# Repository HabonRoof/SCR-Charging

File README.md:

# Sinusoidal Charger with Optimized Frequency Tracking for Li-ion Batteries

The purpose of this thesis is to develop a sinusoidal charger that can track the optimized frequency of Li-ion batteries.
In this study, the optimized AC impedance frequency tracking is firstly carried out for various types of lithium-ion batteries with different aging degrees to achieve the goal of shortening the charging time and increasing the charging efficiency. 
The digital control core of the charger developed in this thesis uses the F280049C digital signal controller (DSC) produced by Texas Instruments and adopts the Powell algorithm to quickly search for the best sinusoidal charging current frequency when the battery state-of-charge (SOC) is 0%, 15% and 30%, which ensures the lowest impedance during charging.
The proposed prototyping circuit uses field effect transistors as voltage-to-current converters and utilizes digital finite impulse response filters and proportional-integral controllers to stabilize the charging current. 
The charger can provide a maximum charging power of 21W. The experimental results show that the proposed sinusoidal charger can shorten the charging time by 3.66%, reduce the charging loss by 1.08% and reduce the temperature rise by 27.16% compared with the traditional constant current and constant voltage charging method.
Keyword: Sinusoidal Charging, Li-ion Batteries, Fast Charging technique, On-line Optimized Impedance Tracking

[Thesis link](https://ndltd.ncl.edu.tw/cgi-bin/gs32/gsweb.cgi/login?o=dwebmge)

# Outlook

# File disceiption
#### AD5940_BATImpedance
- ADICuP3029 project, to control and calculate real/imaginary part of impedance. Include FFT calculation.
- Source code for AD5940 battery EIS measurment module (CN0510), modified and origin by Analog Device .Inc.
#### KiCad
- Schematic file and PCB file for main board, which offer CN0510, F280049C Launch Pad and AD9833 waveform generator module a base.
#### RippleCharging
- The main CCS project folder, control the behavior of sinusoidal charger, waveform generator, MOSFET relay, EIS measurement module.
#### ad5940lib
- Companion library of AD5940_BATImpedance folder

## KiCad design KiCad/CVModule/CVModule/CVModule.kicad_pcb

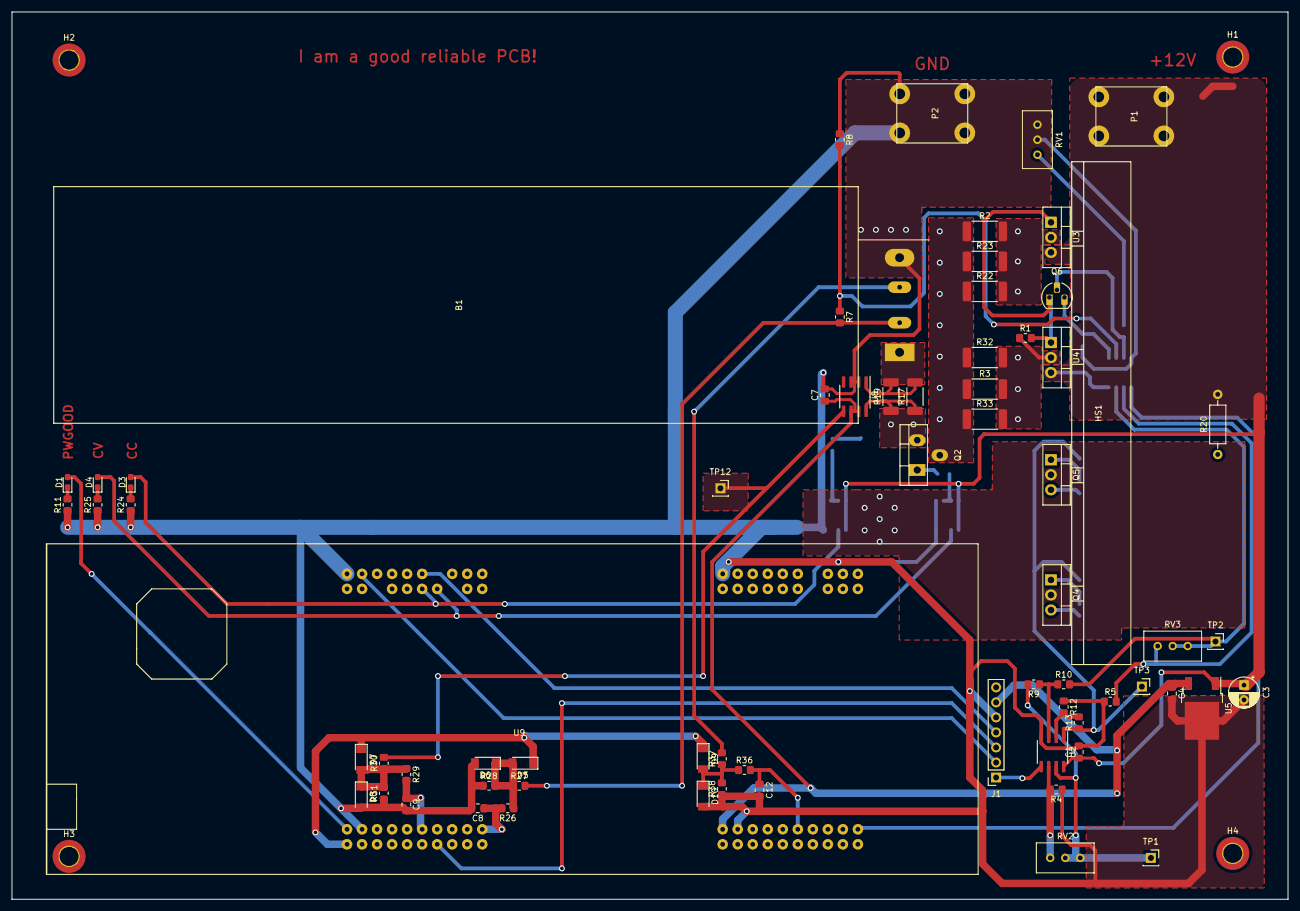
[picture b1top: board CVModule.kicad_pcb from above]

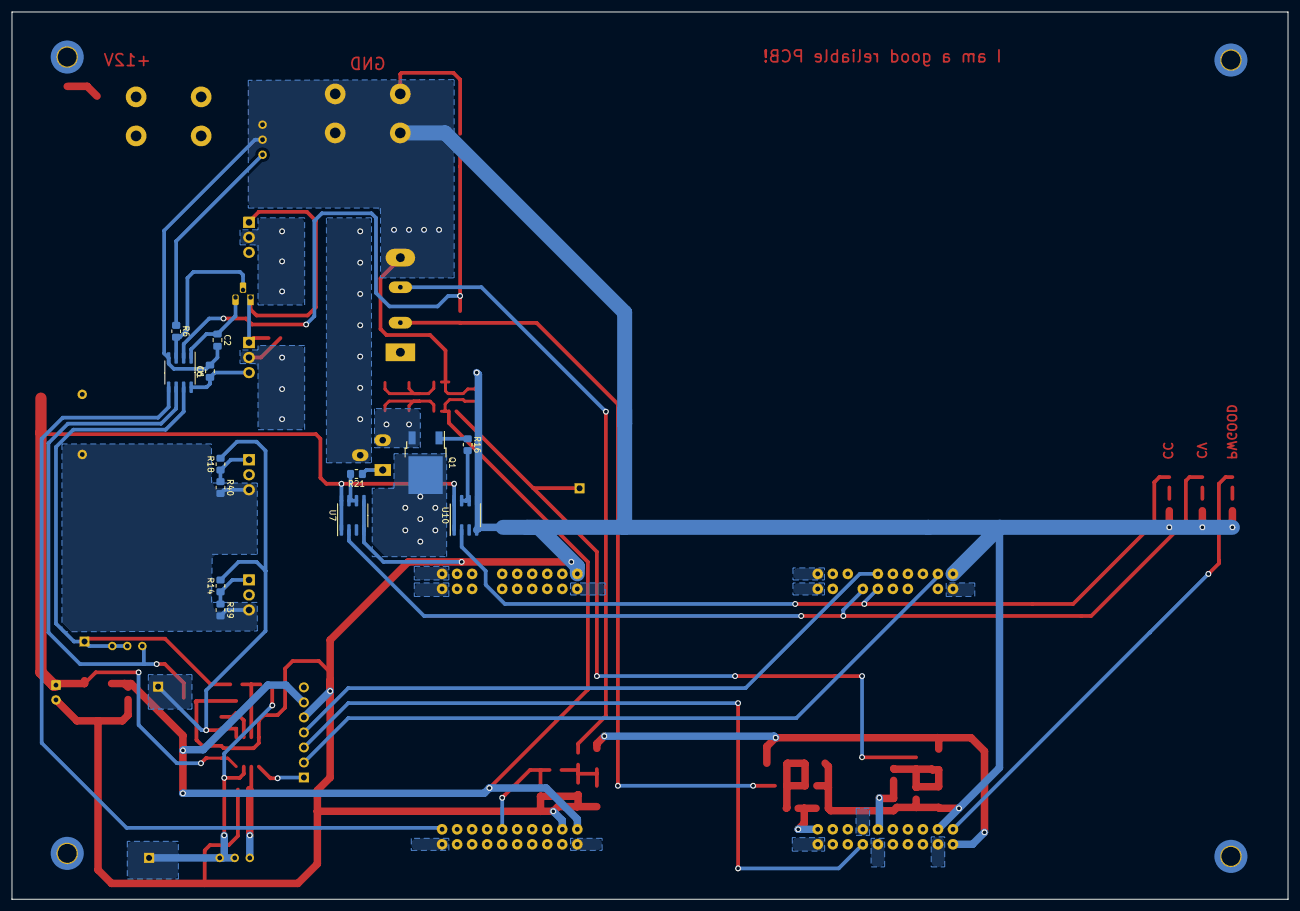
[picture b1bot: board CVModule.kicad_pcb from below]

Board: 2 copper layers, 215.7 x 150.0 mm, 85 parts (13 on the bottom side), 48 nets.

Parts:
B1: BatteryHolder; BatteryHolder-Single
C1, C4, C6, C7, C8, C9, C12: 100n; C_0805_2012Metric_Pad1.18x1.45mm_HandSolder
C2: 180p; C_0805_2012Metric_Pad1.18x1.45mm_HandSolder
C3: 0.33u; CP_Radial_D5.0mm_P2.50mm
D1: GREEN; LED_0603_1608Metric_Pad1.05x0.95mm_HandSolder
D3, D4: RED; LED_0603_1608Metric_Pad1.05x0.95mm_HandSolder
D5, D6, D7, D8, D9, D10: 1N4148; D_MiniMELF
H1, H2, H3, H4: MountingHole; MountingHole_3.2mm_M3_DIN965_Pad_TopBottom
HS1: Heatsink; Heatsink_80mmx3mm_4hole_black
J1: AD9833; PinSocket_1x07_P2.54mm_Vertical
P1: +12Vin; IOPad
P2: GND; IOPad
Q1: 600N25NG; TO-252-2
Q2: IPP030N10N3; TO220-3_Vertical_T
Q4, Q5: IRFR9024; TO-220-3_Vertical
Q6: A733; TO-92_HandSolder
R1, R6: 100; R_0805_2012Metric_Pad1.20x1.40mm_HandSolder
R2, R3, R22, R23, R32, R33: 510m; R_2512_6332Metric_Pad1.40x3.35mm_HandSolder
R4, R11, R12, R24, R25, R26, R29, R36: 1k; R_0805_2012Metric_Pad1.20x1.40mm_HandSolder
R5: 50k; R_0805_2012Metric_Pad1.20x1.40mm_HandSolder
R7, R8: 2M; R_0805_2012Metric_Pad1.20x1.40mm_HandSolder
R9, R10: 100k; R_0805_2012Metric_Pad1.20x1.40mm_HandSolder
R13: 2k; R_0805_2012Metric_Pad1.20x1.40mm_HandSolder
R14, R16, R18, R21: 10; R_0805_2012Metric_Pad1.20x1.40mm_HandSolder
R17, R19: 13m; R_2010_5025Metric_Pad1.40x2.65mm_HandSolder
R20: 0.1/2W; R_Axial_DIN0207_L6.3mm_D2.5mm_P10.16mm_Horizontal
R27, R30, R37: 4.7k; R_0805_2012Metric_Pad1.20x1.40mm_HandSolder
R28, R31, R38, R39, R40: 10k; R_0805_2012Metric_Pad1.20x1.40mm_HandSolder
RV1: 1k; Potentiometer_Bourns_3296W_Vertical
RV2: 2k; Potentiometer_Bourns_3296W_Vertical
RV3: 100k; Potentiometer_Bourns_3296W_Vertical
TP1: sig_TP; PinSocket_1x01_P2.54mm_Vertical
TP2: bias_TP; PinSocket_1x01_P2.54mm_Vertical
TP3: Vg_TP; PinSocket_1x01_P2.54mm_Vertical
TP12: Iout; PinSocket_1x01_P2.54mm_Vertical
U1, U2: LM358; SOIC-8_3.9x4.9mm_P1.27mm
U3, U4: LM317_TO-220; TO-220-3_Vertical
U5: L7805; TO-252-2
U7, U10: TC4420EOA; SOIC-8_3.9x4.9mm_P1.27mm
U8: INA282; SOIC-8_3.9x4.9mm_P1.27mm
U9: LAUNCHXL-F280049C; LANCHXL-F280049C

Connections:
+3V3: D5.1, D7.1, D9.1, U9.1
+4.2V: Q2.2, R2.1, R3.1, R22.1, R23.1, R32.1, R33.1
+5V: C4.1, C7.1, D1.2, J1.6, U5.3, U8.6, U8.7, U9.21, U9.61
+12V: C1.1, C3.1, C6.1, P1.1, R20.2, U1.8, U2.8, U3.3, U4.3, U5.1, U7.1, U7.8, U10.1, U10.8
-BATT: B1.4, C1.2, C2.2, C3.2, C4.2, C6.2, C7.2, C8.2, C9.2, C12.2, D6.2, D8.2, D10.2, J1.5, P2.1, R4.1, R5.1, R8.1, R11.1, R12.1, R24.1, R25.1, R28.1, R31.1, R38.1, RV1.2, RV1.3, U1.4, U2.4, U5.2, U7.4, U7.5, U8.2, U8.3, U9.20, U9.22, U9.60, U9.62, U10.4, U10.5
CC_g: D3.2, U9.35, U10.2
CS: J1.2, U9.19
CV_g: D4.2, U7.2, U9.34
Iout: R30.2, TP12.1, U8.5
MOSI: J1.4, U9.15
unnamed: C2.1, Q6.3, U1.1
unnamed: D1.1, R11.2
unnamed: D3.1, R24.2
unnamed: D4.1, R25.2
unnamed: D5.2, D6.1, R26.1, R27.1, R28.2
unnamed: D7.2, D8.1, R29.1, R30.1, R31.2
unnamed: D9.2, D10.1, R36.1, R37.1, R38.2
unnamed: Q1.1, R16.1
unnamed: Q1.2, Q4.2, Q5.2
unnamed: Q2.1, R21.1
unnamed: Q4.1, R14.1, R39.1
unnamed: Q4.3, Q5.3, R20.1, R39.2, R40.2
unnamed: Q5.1, R18.1, R40.1
unnamed: Q6.1, R1.2, U3.1, U4.1
unnamed: Q6.2, R6.2, U1.3
unnamed: R1.1, R3.2, R32.2, R33.2, U4.2
unnamed: R2.2, R22.2, R23.2, U3.2
unnamed: R4.2, RV2.3, U2.6
unnamed: R5.2, RV3.3, U1.6
unnamed: R6.1, RV1.1
unnamed: R7.1, R8.2, U1.2
unnamed: R9.2, RV2.1, RV2.2, TP1.1, U2.7
unnamed: R9.1, R10.1, U2.3
unnamed: R10.2, RV3.1, RV3.2, TP2.1, U1.7
unnamed: R12.2, R13.2, U2.2
Q1_g: R16.2, U10.6, U10.7
Q2_g: R21.2, U7.6, U7.7
Rs+: Q1.3, Q2.3, R17.1, R19.1, U8.8
Rs-: B1.1, R17.2, R19.2, U8.1
SCLK: J1.3, U9.7
Vbat+: C8.1, R26.2, U9.30
Vbat-: C12.1, R36.2, U9.66
Viout: C9.1, R29.2, U9.26
bat+: B1.2, R7.2, R27.2
bat-: B1.3, R37.2
bias_ctl: U1.5, U9.70
signal: R13.1, R14.2, R18.2, TP3.1, U2.1
sigout: J1.1, U2.5

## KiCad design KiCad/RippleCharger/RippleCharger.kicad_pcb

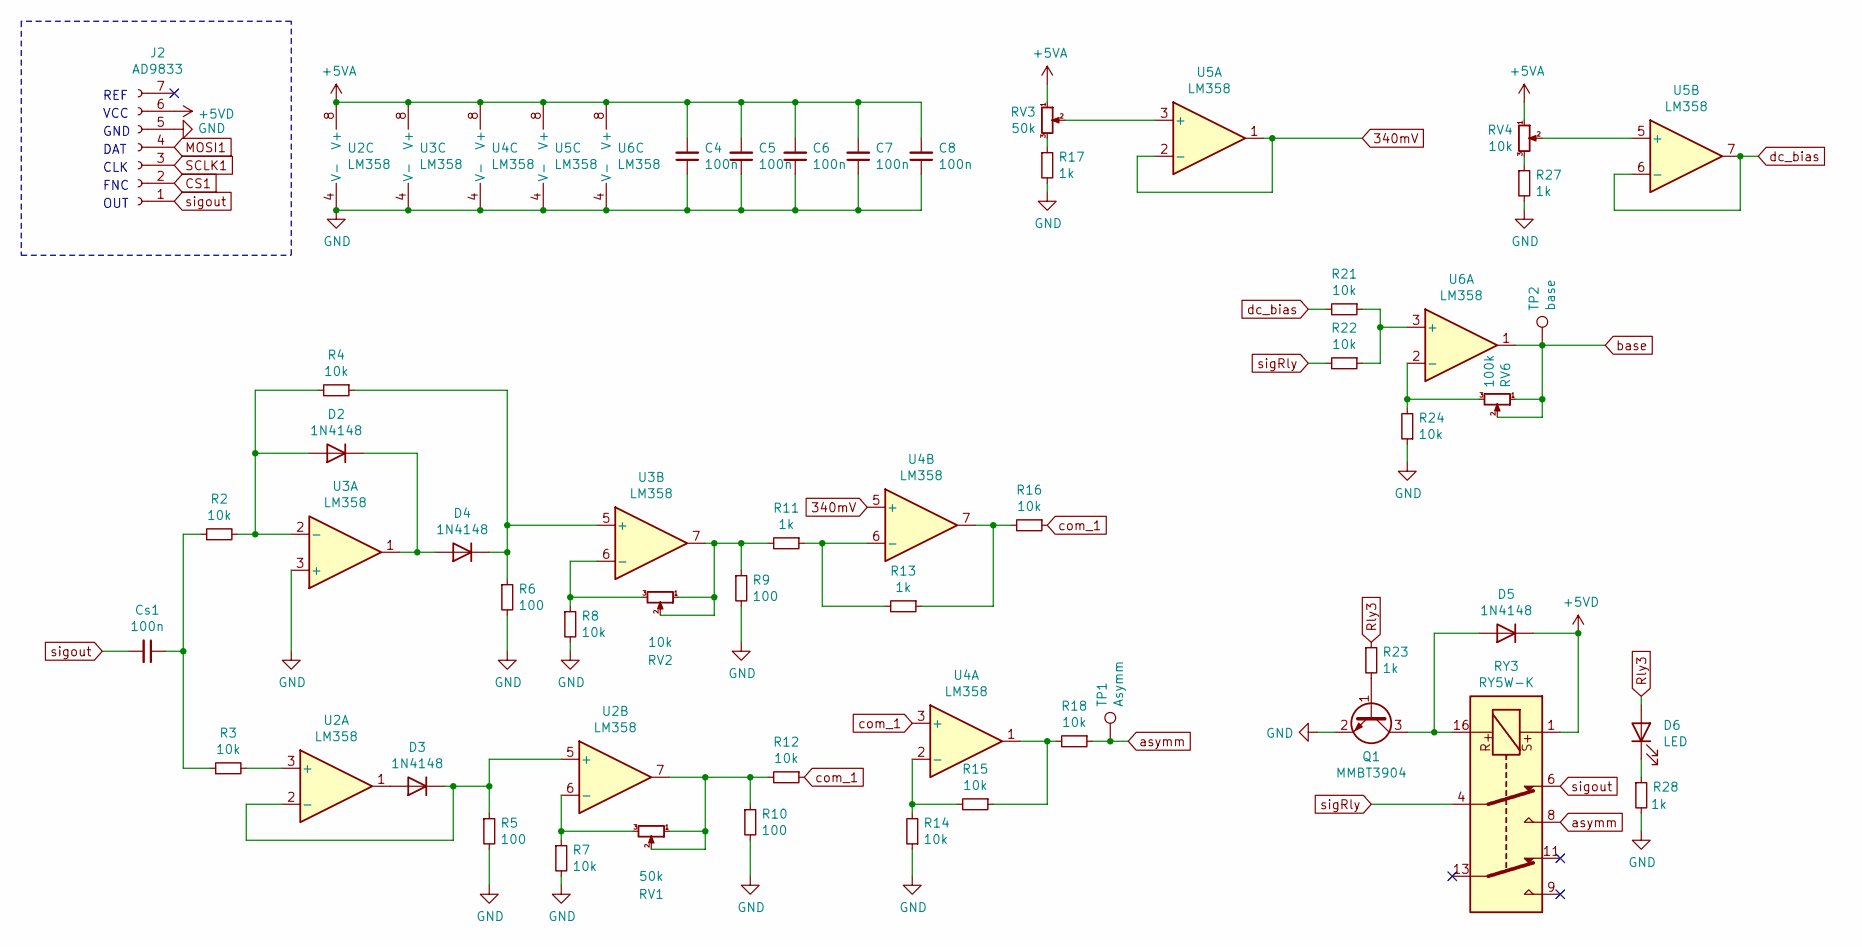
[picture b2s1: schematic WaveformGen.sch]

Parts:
C4, C5, C6, C7, C8: 100n; C_0805_2012Metric_Pad1.18x1.45mm_HandSolder
Cs1: 100n; C_0805_2012Metric_Pad1.18x1.45mm_HandSolder
D2, D3, D4, D5: 1N4148; D_SOD-123
D6: LED; LED_0603_1608Metric_Pad1.05x0.95mm_HandSolder
J2: AD9833; PinHeader_1x07_P2.54mm_Vertical
Q1: MMBT3904; SOT-23
R2, R3, R4, R7, R8, R12, R14, R15, R16, R18, R21, R22, R24: 10k; R_0805_2012Metric_Pad1.20x1.40mm_HandSolder
R5, R6, R9, R10: 100; R_0805_2012Metric_Pad1.20x1.40mm_HandSolder
R11, R13, R17, R23, R27, R28: 1k; R_0805_2012Metric_Pad1.20x1.40mm_HandSolder
RV1, RV3: 50k; Potentiometer_Bourns_3296W_Vertical
RV2, RV4: 10k; Potentiometer_Bourns_3296W_Vertical
RV6: 100k; Potentiometer_Bourns_3296W_Vertical
RY3: RY5W-K
TP1: Asymm; PinHeader_1x01_P2.54mm_Vertical
TP2: base; PinHeader_1x01_P2.54mm_Vertical
U2, U3, U4, U5, U6: LM358; SOIC-8_3.9x4.9mm_P1.27mm

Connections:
340mV: U4.5 (+), U5.1, U5.2 (-)
+5VA: C4.2, C5.2, C6.2, C7.2, C8.2, RV3.1, RV4.1, U2.8 (V+), U3.8 (V+), U4.8 (V+), U5.8 (V+), U6.8 (V+); also elsewhere on the board
+5VD: D5.1 (K), J2.6, RY3.1; also elsewhere on the board
CS1: J2.2; also elsewhere on the board
GND: C4.1, C5.1, C6.1, C7.1, C8.1, J2.5, Q1.2 (E), R5.2, R6.2, R7.2, R8.2, R9.2, R10.2, R14.1, R17.2, R24.1, R27.2, R28.2, U2.4 (V-), U3.3 (+), U3.4 (V-), U4.4 (V-), U5.4 (V-), U6.4 (V-); also elsewhere on the board
MOSI1: J2.4; also elsewhere on the board
unnamed: Cs1.1, R2.1, R3.1
unnamed: D2.1 (K), D4.2 (A), U3.1
unnamed: D2.2 (A), R2.2, R4.2, U3.2 (-)
unnamed: D3.1 (K), R5.1, U2.2 (-), U2.5 (+)
unnamed: D3.2 (A), U2.1
unnamed: D4.1 (K), R4.1, R6.1, U3.5 (+)
unnamed: D5.2 (A), Q1.3 (C), RY3.16
unnamed: D6.1 (K), R28.1
unnamed: Q1.1 (B), R23.2
unnamed: R3.2, U2.3 (+)
unnamed: R7.1, RV1.3, U2.6 (-)
unnamed: R8.1, RV2.3, U3.6 (-)
unnamed: R10.1, R12.2, RV1.1, RV1.2, U2.7
unnamed: R11.1, R13.2, U4.6 (-)
unnamed: R9.1, R11.2, RV2.1, RV2.2, U3.7
unnamed: R13.1, R16.2, U4.7
unnamed: R14.2, R15.2, U4.2 (-)
unnamed: R15.1, R18.2, U4.1
unnamed: R17.1, RV3.3
unnamed: R21.1, R22.1, U6.3 (+)
unnamed: R24.2, RV6.3, U6.2 (-)
unnamed: R27.1, RV4.3
unnamed: RV3.2, U5.3 (+)
unnamed: RV4.2, U5.5 (+)
Rly3: D6.2 (A), R23.1; also elsewhere on the board
SCLK1: J2.3; also elsewhere on the board
asymm: R18.1, RY3.8, TP1.1
base: RV6.1, RV6.2, TP2.1, U6.1; also elsewhere on the board
com_1: R12.1, R16.1, U4.3 (+)
dc_bias: R21.2, U5.6 (-), U5.7
sigRly: R22.2, RY3.4
sigout: Cs1.2, J2.1, RY3.6

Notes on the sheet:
REF
VCC
GND
DAT
CLK
FNC
OUT

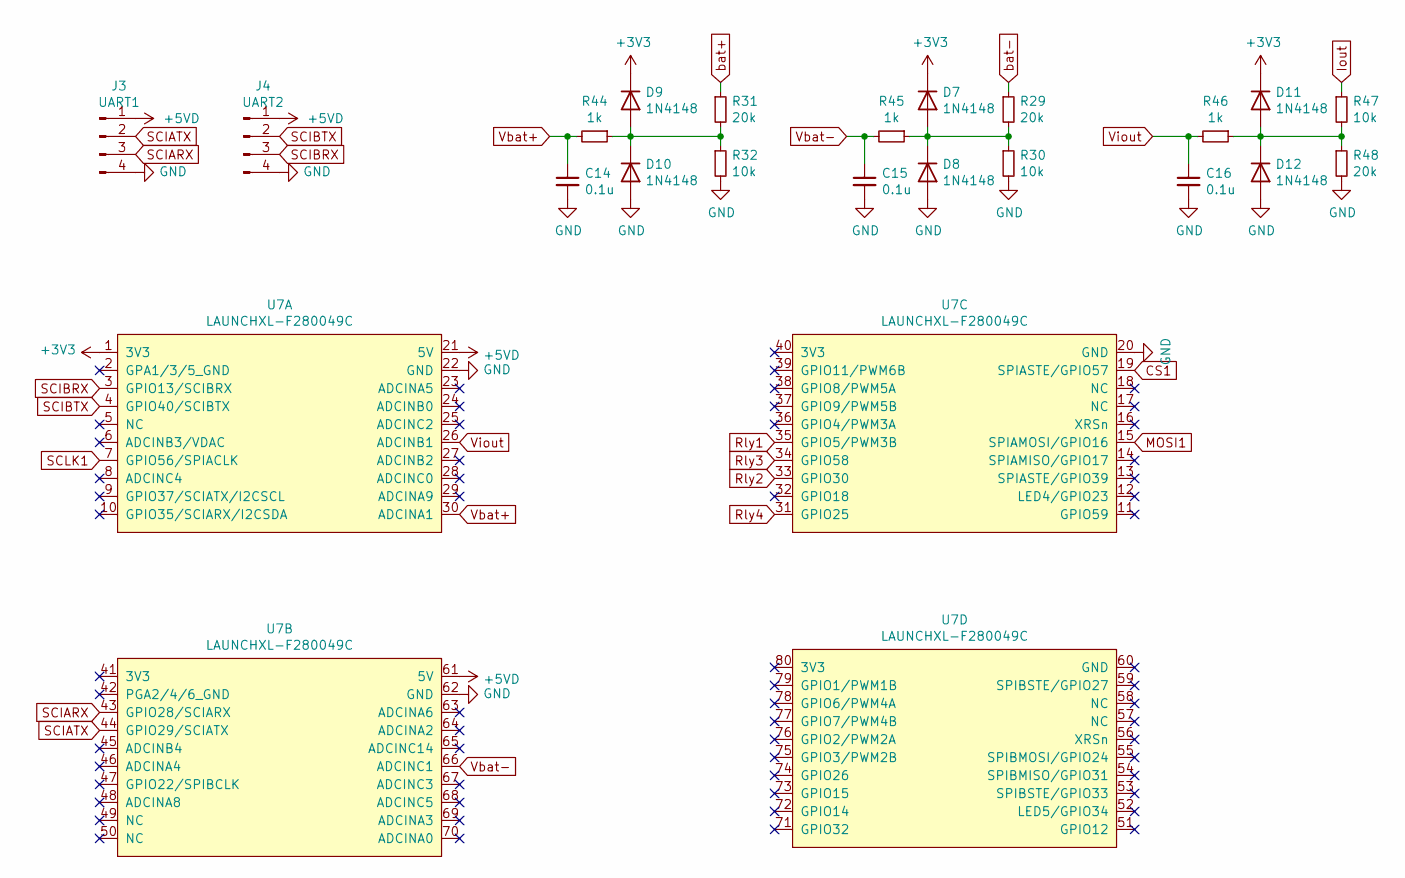
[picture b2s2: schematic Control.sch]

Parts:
C14, C15, C16: 0.1u; C_0805_2012Metric_Pad1.18x1.45mm_HandSolder
D7, D8, D9, D10, D11, D12: 1N4148; D_SOD-123
J3: UART1; PinHeader_1x04_P2.54mm_Vertical
J4: UART2; PinHeader_1x04_P2.54mm_Vertical
R29, R31, R48: 20k; R_0805_2012Metric_Pad1.20x1.40mm_HandSolder
R30, R32, R47: 10k; R_0805_2012Metric_Pad1.20x1.40mm_HandSolder
R44, R45, R46: 1k; R_0805_2012Metric_Pad1.20x1.40mm_HandSolder
U7: LAUNCHXL-F280049C; LANCHXL-F280049C

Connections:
+3V3: D7.1 (K), D9.1 (K), D11.1 (K), U7.1 (3V3)
+5VD: J3.1, J4.1, U7.21 (5V), U7.61 (5V); also elsewhere on the board
CS1: U7.19 (SPIASTE/GPIO57); also elsewhere on the board
GND: C14.2, C15.2, C16.2, D8.2 (A), D10.2 (A), D12.2 (A), J3.4, J4.4, R30.2, R32.2, R48.2, U7.20 (GND), U7.22 (GND), U7.62 (GND); also elsewhere on the board
MOSI1: U7.15 (SPIAMOSI/GPIO16); also elsewhere on the board
unnamed: D7.2 (A), D8.1 (K), R29.2, R30.1, R45.1
unnamed: D9.2 (A), D10.1 (K), R31.2, R32.1, R44.1
unnamed: D11.2 (A), D12.1 (K), R46.1, R47.2, R48.1
Rly1: U7.35 (GPIO5/PWM3B); also elsewhere on the board
Rly2: U7.33 (GPIO30); also elsewhere on the board
Rly3: U7.34 (GPIO58); also elsewhere on the board
Rly4: U7.31 (GPIO25); also elsewhere on the board
SCIARX: J3.3, U7.43 (GPIO28/SCIARX)
SCIATX: J3.2, U7.44 (GPIO29/SCIATX)
SCIBRX: J4.3, U7.3 (GPIO13/SCIBRX)
SCIBTX: J4.2, U7.4 (GPIO40/SCIBTX)
SCLK1: U7.7 (GPIO56/SPIACLK); also elsewhere on the board
Vbat+: C14.1, R44.2, U7.30 (ADCINA1)
Vbat-: C15.1, R45.2, U7.66 (ADCINC1)
Viout: C16.1, R46.2, U7.26 (ADCINB1)
bat+: R31.1; also elsewhere on the board
bat-: R29.1; also elsewhere on the board

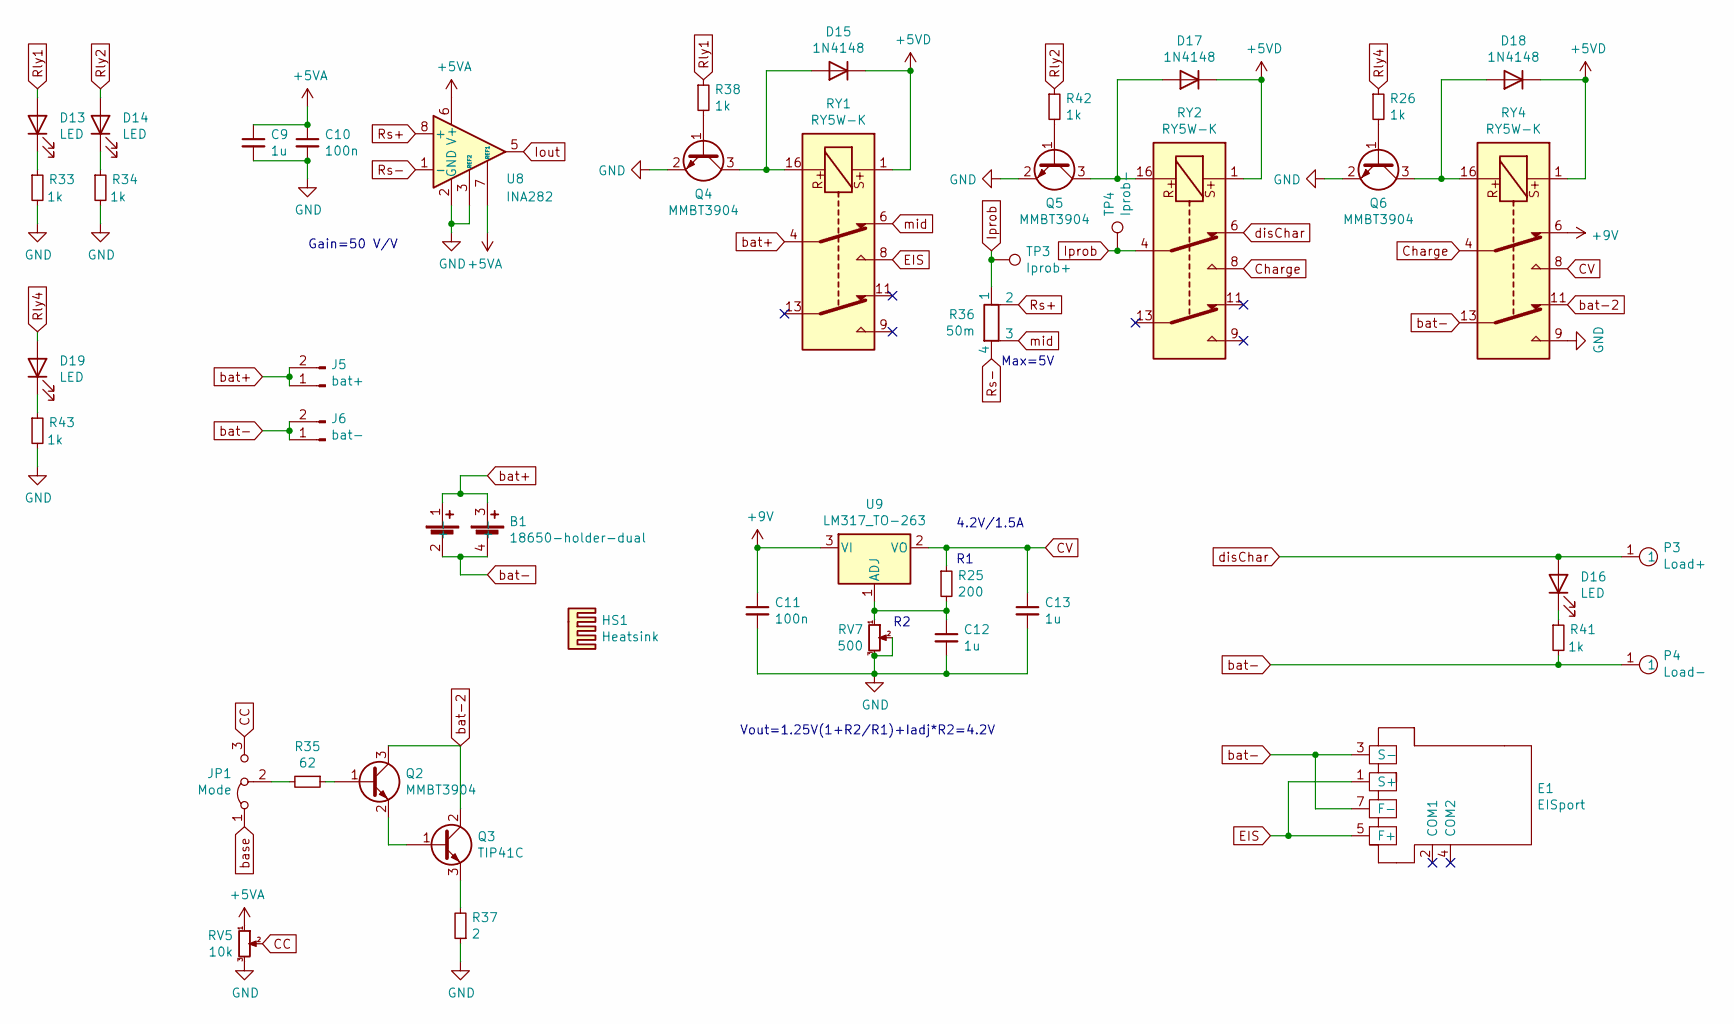
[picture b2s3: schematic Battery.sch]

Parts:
B1: 18650-holder-dual
C9, C12, C13: 1u; C_0805_2012Metric_Pad1.18x1.45mm_HandSolder
C10, C11: 100n; C_0805_2012Metric_Pad1.18x1.45mm_HandSolder
D13, D14, D19: LED; LED_0603_1608Metric_Pad1.05x0.95mm_HandSolder
D15, D17, D18: 1N4148; D_SOD-123
D16: LED; LED_D3.0mm
E1: EISport; CN0510_BNC
HS1: Heatsink; Heatsink_Fischer_SK104-STCB_35x13mm__2xDrill3.5mm_ScrewM3
J5: bat+; PinHeader_1x02_P2.54mm_Vertical
J6: bat-; PinHeader_1x02_P2.54mm_Vertical
JP1: Mode; PinHeader_1x03_P2.54mm_Vertical
P3: Load+; IOPad
P4: Load-; IOPad
Q2, Q4, Q5, Q6: MMBT3904; SOT-23
Q3: TIP41C; TO-220-3_Vertical
R25: 200; R_0805_2012Metric_Pad1.20x1.40mm_HandSolder
R26, R33, R34, R38, R41, R42, R43: 1k; R_0805_2012Metric_Pad1.20x1.40mm_HandSolder
R35: 62; R_0805_2012Metric_Pad1.20x1.40mm_HandSolder
R36: 50m; R_Shunt_Ohmite_LVK24
R37: 2; R_Axial_Power_L20.0mm_W6.4mm_P25.40mm
RV5: 10k; Potentiometer_Bourns_3296W_Vertical
RV7: 500; Potentiometer_Bourns_3296W_Vertical
RY1, RY2, RY4: RY5W-K
TP3: Iprob+; PinHeader_1x01_P2.54mm_Vertical
TP4: Iprob-; PinHeader_1x01_P2.54mm_Vertical
U8: INA282; SOIC-8_3.9x4.9mm_P1.27mm
U9: LM317_TO-263; TO-263-2

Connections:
+5VA: C9.1, C10.1, RV5.1, U8.6 (V+), U8.7 (REF1); also elsewhere on the board
+5VD: D15.1 (K), D17.1 (K), D18.1 (K), RY1.1, RY2.1, RY4.1; also elsewhere on the board
+9V: C11.1, RY4.6, U9.3 (VI); also elsewhere on the board
CC: JP1.3 (B), RV5.2
CV: C13.1, R25.1, RY4.8, U9.2 (VO)
Charge: RY2.8, RY4.4
EIS: E1.1 (S+), E1.5 (F+), RY1.8
GND: C9.2, C10.2, C11.2, C12.2, C13.2, Q4.2 (E), Q5.2 (E), Q6.2 (E), R33.2, R34.2, R37.1, R43.2, RV5.3, RV7.2, RV7.3, RY4.9, U8.2 (GND), U8.3 (REF2); also elsewhere on the board
unnamed: C12.1, R25.2, RV7.1, U9.1 (ADJ)
unnamed: D13.1 (K), R33.1
unnamed: D14.1 (K), R34.1
unnamed: D15.2 (A), Q4.3 (C), RY1.16
unnamed: D16.1 (K), R41.1
unnamed: D17.2 (A), Q5.3 (C), RY2.16
unnamed: D18.2 (A), Q6.3 (C), RY4.16
unnamed: D19.1 (K), R43.1
unnamed: JP1.2 (C), R35.2
unnamed: Q2.1 (B), R35.1
unnamed: Q2.2 (E), Q3.1 (B)
unnamed: Q3.3 (E), R37.2
unnamed: Q4.1 (B), R38.2
unnamed: Q5.1 (B), R42.2
unnamed: Q6.1 (B), R26.2
Rly1: D13.2 (A), R38.1; also elsewhere on the board
Rly2: D14.2 (A), R42.1; also elsewhere on the board
Rly4: D19.2 (A), R26.1; also elsewhere on the board
Rs+: R36.2, U8.8 (+)
Rs-: R36.4, U8.1 (-)
base: JP1.1 (A); also elsewhere on the board
bat+: B1.1 (+), B1.3 (+), J5.1, J5.2, RY1.4; also elsewhere on the board
bat-: B1.2 (-), B1.4 (-), E1.3 (S-), E1.7 (F-), J6.1, J6.2, P4.1, R41.2, RY4.13; also elsewhere on the board
bat-2: Q2.3 (C), Q3.2 (C), RY4.11
disChar: D16.2 (A), P3.1, RY2.6
mid: R36.3, RY1.6

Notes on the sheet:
Gain=50 V/V
Max=5V
Vout=1.25V(1+R2/R1)+Iadj*R2=4.2V
4.2V/1.5A

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
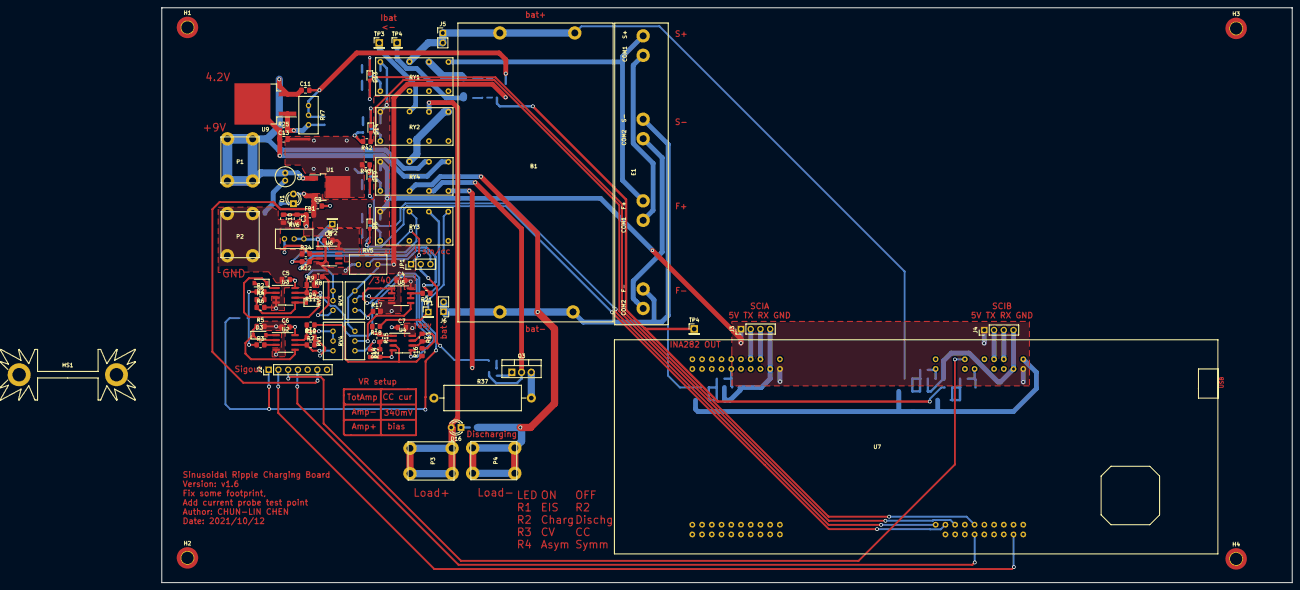
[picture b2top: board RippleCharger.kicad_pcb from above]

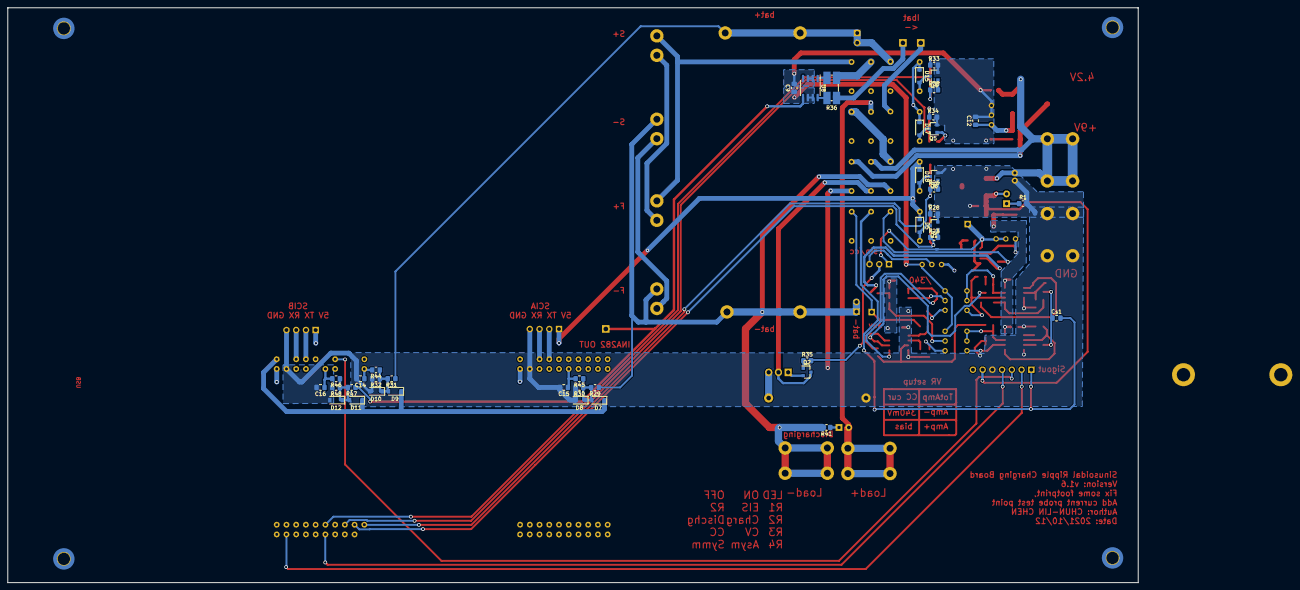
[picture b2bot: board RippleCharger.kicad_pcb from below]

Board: 2 copper layers, 295.0 x 150.0 mm, 129 parts (41 on the bottom side), 82 nets.

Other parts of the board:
C1: 0.33u; C_Radial_D5.0mm_H11.0mm_P2.00mm
C2, C3: 0.1u; C_0805_2012Metric_Pad1.18x1.45mm_HandSolder
D1: LED; LED_D3.0mm
FB1: Ferrite_Bead_Small; R_0805_2012Metric_Pad1.20x1.40mm_HandSolder
H1, H2, H3, H4: MountingHole; MountingHole_3.2mm_M3_DIN965_Pad_TopBottom
P1, P2: IOPad
R1: 1k; R_0805_2012Metric_Pad1.20x1.40mm_HandSolder
TP4#2: Iprob-; PinHeader_1x01_P2.54mm_Vertical
U1: L7805; TO-252-2

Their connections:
+5VA: C3.1, FB1.1; also elsewhere on the board
+5VD: C2.1, D1.2, FB1.2, U1.3; also elsewhere on the board
+9V: C1.1, P1.1, U1.1; also elsewhere on the board
GND: C1.2, C2.2, C3.2, P2.1, R1.2, U1.2; also elsewhere on the board
unnamed: D1.1, R1.1

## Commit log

2021-09-23 Add ADICUP3029 EIS base board firmware
2021-09-23 Add ADICUP3029 source code
2021-09-23 Correct the path
2021-10-15 Update PCB layout m include relay footprint, board outlook.Modify Main 0049 code and add CV function
2021-10-15 Fix CV charging route
2021-10-25 Fix Layout error and adjust firmware ADC tradshold
2021-10-26 Add UART function into F280049, and fix the CV status ADC value. Change ADICUP3029 baudrate, modify UART return character into \r\n
2021-11-22 Modify SRC charging code, Modify CN0510 code add CLI driver from original source
2021-11-22 Add new SRC CCCV board, add battery holder footpront into library
2021-12-27 Fix single frequency test accuricy and add uart driver into ADICUP3029 code
2022-01-10 Add UART communication in 3029, transmit and receive command successfully but not implement impedance request yet
2022-01-11 Fix uart FIFO issue, optimize 3029 uart RXIST size,implement AppBATCfg modifier, move IDE project location into git directory, remove none used file
2022-01-12 Remove ignored files
2022-01-18 Add single frequency test function, re-measure AppBATCfg.RcalVolt every time when frequency updated by UART from TI MCU. Reduce PreCharge function delay time to speedup measurement performence. ISSUE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
2022-01-20 Add dual slope search method, fix bug of transmit float to 3029
2022-01-21 Add P&O method in the end of dual slope search, fix impIdx duplicate issue
2022-03-05 Add coulomb integral in main loop, add three level SRC at 30,60% SOC, temporary disable EIS measuring func
2022-03-17 Change FIR cutoff frequency, add pid controller to stablize current at 2.6A
2023-03-07 Add outlook picture of project
